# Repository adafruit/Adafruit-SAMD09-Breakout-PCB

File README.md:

## Adafruit SAMD09 Breakout PCB

<a href="http://www.adafruit.com/products/3657"><br/>
Click here to purchase one from the Adafruit shop</a>

PCB files for the Adafruit SAMD09 microcontroller breakout

Format is EagleCAD schematic and board layout

For more details, check out the product page at
* https://www.adafruit.com/products/3657

### Description

Adafruit seesaw is a near-universal converter framework which allows you to add add and extend hardware support to any I2C-capable microcontroller or microcomputer. Instead of getting separate I2C GPIO expanders, ADCs, PWM drivers, etc, seesaw can be configured to give a wide range of capabilities.

For example, our ATSAMD09 breakout with seesaw gives you

* 3 x 12-bit ADC inputs
* 3 x 8-bit PWM outputs
* 7 x GPIO with selectable pullup or pulldown
* 1 x NeoPixel output (up to 340 pixels)
* 1 x EEPROM with 64 byte of NVM memory (handy for storing small access tokens or MAC addresses)
* 1 x Interrupt output that can be triggered by any of the accessories
* 2 x I2C address selection pins
* 1 x Activity LED

But you can reprogram and reconfigure the chip to have more or less of each peripheral - as long as it fits into the ATSAMD09D14's firmware! For example, there's also a UART converter but it isn't included in the default firmware.

The ATSAMD09 breakout is great for development of seesaw capabilities (we use it in-house for our design work) or you can use it as-is to give your Raspberry Pi or ESP8266 more hardware support! Each breakout comes with the assembled and tested board, as well as some header strips.

Please note: The boards do not come with a bootloader. If you want to do development on seesaw (e.g. changing the configuration) you'll need to pick up a J-Link and we recommend a SWD adapter breakout. 

### License

Adafruit invests time and resources providing this open source design, please support Adafruit and open-source hardware by purchasing products from [Adafruit](https://www.adafruit.com)!

Designed by Limor Fried/Ladyada for Adafruit Industries.

Creative Commons Attribution/Share-Alike, all text above must be included in any redistribution. See license.txt for additional details.

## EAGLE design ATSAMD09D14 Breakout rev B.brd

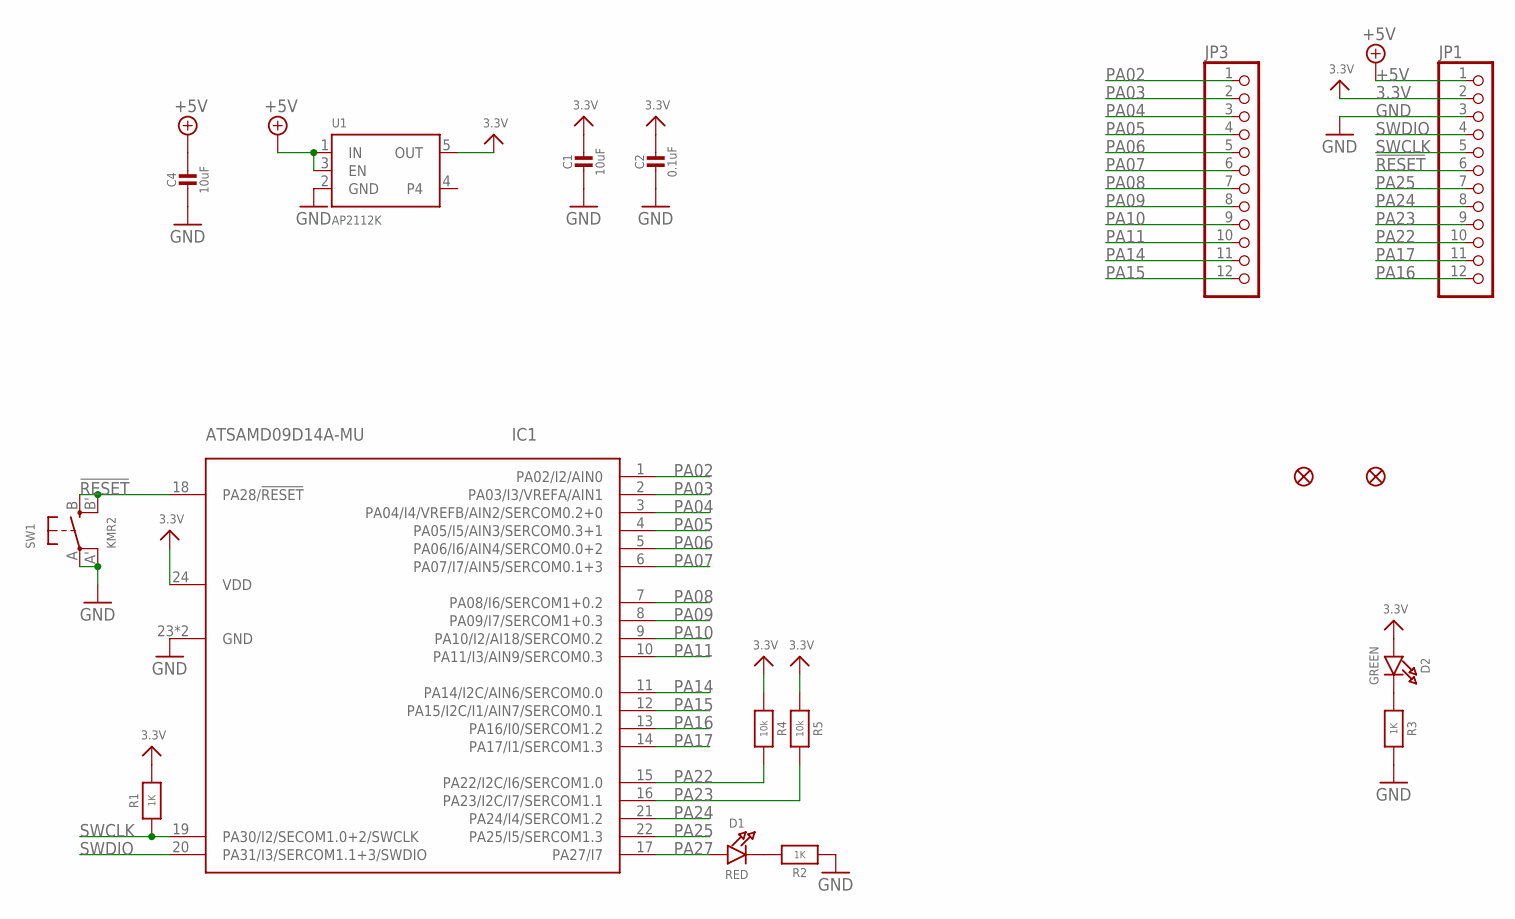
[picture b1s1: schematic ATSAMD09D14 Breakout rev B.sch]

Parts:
C1, C4: 10uF; 0805-NO
C2: 0.1uF; 0603-NO
D1: RED; CHIPLED_0805_NOOUTLINE
D2: GREEN; CHIPLED_0805_NOOUTLINE
FID1, FID2: FIDUCIAL""; FIDUCIAL_1MM
IC1: ATSAMD09D14A-MU; QFN24_4MM
JP1, JP3: HEADER-1X1276MIL; 1X12_ROUND_76MIL
R1, R2, R3: 1K; 0603-NO
R4, R5: 10k; 0603-NO
SW1: KMR2; BTN_KMR2_4.6X2.8
U1: AP2112K; SOT23-5

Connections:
3.3V: C1.1, C2.1, D2.A, IC1.24 (VDD), JP1.2, R1.2, R4.1, R5.1, U1.5 (OUT)
!RESET: IC1.18 (PA28/!RESET), JP1.6, SW1.B (S), SW1.B' (S1)
+5V: C4.1, JP1.1, U1.1 (IN), U1.3 (EN)
GND: C1.2, C2.2, C4.2, IC1.23 (GND), IC1.THERM (GND), JP1.3, R2.1, R3.2, SW1.A, SW1.A' (P1), U1.2 (GND)
unnamed: D1.C, R2.2
unnamed: D2.C, R3.1
PA02: IC1.1 (PA02/I2/AIN0), JP3.1
PA03: IC1.2 (PA03/I3/VREFA/AIN1), JP3.2
PA04: IC1.3 (PA04/I4/VREFB/AIN2/SERCOM0.2+0), JP3.3
PA05: IC1.4 (PA05/I5/AIN3/SERCOM0.3+1), JP3.4
PA06: IC1.5 (PA06/I6/AIN4/SERCOM0.0+2), JP3.5
PA07: IC1.6 (PA07/I7/AIN5/SERCOM0.1+3), JP3.6
PA08: IC1.7 (PA08/I6/SERCOM1+0.2), JP3.7
PA09: IC1.8 (PA09/I7/SERCOM1+0.3), JP3.8
PA10: IC1.9 (PA10/I2/AI18/SERCOM0.2), JP3.9
PA11: IC1.10 (PA11/I3/AIN9/SERCOM0.3), JP3.10
PA14: IC1.11 (PA14/I2C/AIN6/SERCOM0.0), JP3.11
PA15: IC1.12 (PA15/I2C/I1/AIN7/SERCOM0.1), JP3.12
PA16: IC1.13 (PA16/I0/SERCOM1.2), JP1.12
PA17: IC1.14 (PA17/I1/SERCOM1.3), JP1.11
PA22: IC1.15 (PA22/I2C/I6/SERCOM1.0), JP1.10, R4.2
PA23: IC1.16 (PA23/I2C/I7/SERCOM1.1), JP1.9, R5.2
PA24: IC1.21 (PA24/I4/SERCOM1.2), JP1.8
PA25: IC1.22 (PA25/I5/SERCOM1.3), JP1.7
PA27: D1.A, IC1.17 (PA27/I7)
SWCLK: IC1.19 (PA30/I2/SECOM1.0+2/SWCLK), JP1.5, R1.1
SWDIO: IC1.20 (PA31/I3/SERCOM1.1+3/SWDIO), JP1.4

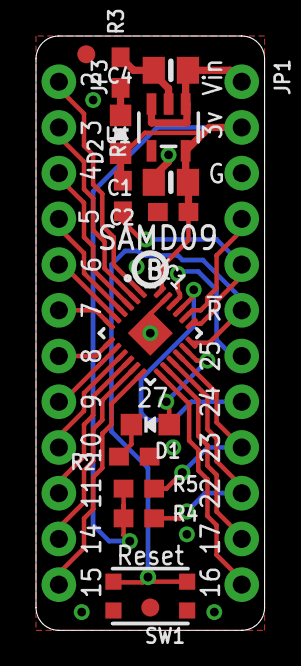
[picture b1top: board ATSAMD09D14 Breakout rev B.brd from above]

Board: 2 copper layers, 12.7 x 33.0 mm, 19 parts (1 on the bottom side), 27 nets.

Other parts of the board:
U$7: SEESAW_LOGO
U$12: PCBFEAT-REV-040

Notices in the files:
parts and their libraries:
microbuilder: This work is placed in the public domain, and may be freely used for commercial and non-commercial work with the following conditions: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
